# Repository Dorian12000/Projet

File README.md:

# Robot Chat et Souris

Ce projet consiste à créer un robot capable de jouer au jeu du chat et de la souris. Le robot est équipé de plusieurs fonctionnalités clés, notamment le contrôle de mouvement à l'aide de moteurs à courant continu (MCC), la localisation avec un Lidar YD X4, la détection du vide à l'aide de capteurs de bordure et le changement d'état ( Souris , Chat) grâce aux bumpers. 

## Schéma Fonctionnel : 
https://miro.com/app/dashboard/

## Fonctionnalités principales

1. **Contrôle de Mouvement (MCC) :**
   - Le robot est capable de se déplacer dans son environnement grâce à des moteurs à courant continu. 
2. **Localisation avec Lidar X4 :**
   - Utilisation du Lidar X4 pour permettre au robot de s'orienter et de se repérer dans son environnement.

3. **Détection du Vide avec Capteurs de Bordure et Changement d'état :**
   - Les capteurs de bordure sont utilisés pour détecter les zones sans sol, afin d'empêcher le robot de tomber.
   - Changement d'états (Souris, Chat) grâce aux bumpers : Utilisation de  bumpers placés sur chaque côté du robot. Lorsqu'un des bumpers est touché, on change  l'état du robot. 

## Utilisation

1. **Exécution du Programme :**
   - Pour démarrer le robot, exécutez le programme principal. Assurez-vous que toutes les dépendances sont installées et que le robot est correctement alimenté. Le robot démarre en mode Souris.

2. **Interface Utilisateur :**
   - Pour connaître les événements enregistrés par le robot, veuillez connecter une ST-link entre le robot et votre ordinateur, puis ouvrir une console (TeraTerm, Putty, ...) configurée en 115200 bauds.
   - Trois LEDs sont présentes sur le robot pour indiquer son état en temps réel :
        - Led verte :
        	- allumée : état chat
        	- éteinte : état souris
        - Led orange : changement d'état pour chaque détection de bordure.
        - Led rouge : le robot a rencontré un problème et doit être redémarré.

## Pilote Lidar pour système robotique

1. **Introduction :**

Le pilote Lidar consiste en l'intégration d'un lidar dans un système robotique tel que notre robot. Le lidar est utilisé pour la détection d'obstacles, la cartographie de l'environnement et la localisation des autres robots dans la zone d'opération. Ce document fournit des informations sur les fichiers principaux du projet, y compris les fichiers `drv_lidar.c`, `LidarTask.c`, et la création de la tâche Lidar.

2. **Contenu des fichiers :**

	#### `drv_lidar.c`

	Le fichier `drv_lidar.c` contient le code source pour le pilote du lidar. Il comprend les fonctionnalités suivantes :

	- **Initialisation du Lidar** : La fonction `LidarInit` initialise le lidar en configurant la communication UART, en créant un sémaphore pour la synchronisation des lectures UART, et en activant le l'échantillonage du lidar et son moteur.

	- **Communication UART** : Le fichier utilise la communication UART avec le mécanisme DMA pour une transmission et réception de données efficace et non bloquante.

	- **Commandes Lidar** : Les fonctions `LidarScanStart` et `LidarScanStop` envoient respectivement les commandes de démarrage et d'arrêt du scan au lidar.

	- **Traitement des données** : Les fonctions `getLidarScanData`, `checkCS` et `convertSample` sont responsables de la réception, de la vérification de la somme de contrôle et de la conversion des données de scan du lidar.

	- **Analyse des données Lidar** : La fonction `whereIsNearestRobot` analyse les données du lidar pour déterminer la position du robot le plus proche.

	- **Gestion des erreurs** : La fonction `LidarHealthStatus` permet d'obtenir le statut de santé du lidar et de gérer les erreurs éventuelles.

	- **Autres fonctionnalités** : Le fichier contient également des fonctions pour définir la vitesse du lidar, obtenir des informations sur le lidar et redémarrer le lidar.

	#### `LidarTask.c`

	Le fichier `LidarTask.c` contient la définition de la tâche Lidar. Il gère les états de la tâche, notamment l'initialisation du lidar, le scan, le traitement des données et le mode veille.

	- **États de la tâche** : Les états comprennent l'initialisation (`LIDAR_INIT`), le scan (`LIDAR_SCANNING`) et le mode veille (`LIDAR_STANDBY`).

	- **Initialisation** : La tâche commence par initialiser le lidar, récupérer des informations sur le lidar afin d'assurer son bon fonctionnement, puis passer à l'état de scan.

	- **Scan Lidar** : Dans cet état, la tâche démarre le scan du lidar, reçoit les données de scan, les traite et effectue des actions en fonction de l'état principal du système (CAT ou MOUSE).

	- **Mode veille** : Un état futur pour le mode veille est également prévu mais n'est pas encore implémenté.

	- **Gestion des erreurs** : En cas d'erreur lors du scan, la tâche passe à l'état d'erreur pour gérer la situation.

3. **Utilisation du code :**

	- **Création de la tâche Lidar** : La fonction `createLidarTask` dans `LidarTask.c` crée la tâche Lidar en utilisant FreeRTOS. Elle définit la profondeur de la pile et la priorité de la tâche.

	- **Configuration du Lidar** : Le fichier `drv_lidar.c` comprend des fonctions pour l'initialisation du lidar, la configuration de la vitesse du moteur, le démarrage et l'arrêt du scan, l'obtention d'informations, la récupération des données de scan, etc.

	- **Gestion des états** : La tâche Lidar gère différents états, tels que l'initialisation, le scan et la veille. Ces états sont définis dans `LidarTask.c` et peuvent être étendus selon les besoins.

	- **Analyse des données** : La fonction `whereIsNearestRobot` analyse les données du lidar pour déterminer la position du robot le plus proche. Cette fonction peut être adaptée en fonction des exigences spécifiques du projet.

4. **Remarques :**

	- Le pilote du lidar est conçu pour fonctionner avec FreeRTOS. Assurez-vous que votre projet est configuré pour utiliser FreeRTOS.

	- La communication avec le lidar utilise le DMA pour une transmission et une réception de données efficaces et non bloquantes via UART.

	- La fonction principale de la tâche Lidar est gérée par la fonction `lidarTask()`, qui comprend une machine d'états pour gérer les différents états du lidar.

	- La tâche Lidar s'exécute en boucle continue, surveillant et gérant l'état du dispositif lidar.

	- Des types de données personnalisés et des macros de journalisation sont définis dans `types.h` et `logger.h`, respectivement.

# Organisation des tâches 

Pour organiser nos tâches liées aux différentes fonctions du Lidar et des moteurs, nous avons crée une tache principale avec une priorité élevée ( code source dans mainTask.c). Cette tâche est divisé en plusieurs états :
   - Main Init : Initialisation des tâches de démarrage du Lidar, des moteurs et de l'asservissement.
   - ERROR : Gestion d'erreur
   - Mouse : Test de l'état avec une Led
   - CAT : Test de l'état avec une Led
( Pour l'état CAT/MOUSE, des notifications sont générées lorsque les bumpers sont appuyés)

Chaque état implique l'appels des tâches et des fonctions nécessaires. Un timer est configuré pour suivre l'état actuel du robot.

## Contrôle moteur et asservissement en vitesse

Les deux MCC sont controlés par des pwm et asservis en vitesse par un correcteur proportionnel dans une tâche.

1. **Driver de moteur :**

   Les fichiers `moteur_drv.c/.h` contiennent les fonctions permettant de commander la vitesse ainsi que les directions des moteurs et de générer les pwm en conséquence. Ils prévoient aussi le calcul de la vitesse des moteurs et la lecture des encodeurs.

2. **Conversion de la position visée en commande de vitesse pour les moteurs :**

   	Cette tâche reçoit une structure comprenant la position (angle et distance) à laquelle doit se rendre le robot. Ces données sont interprétées pour générer une commande (vitesse et sens de rotation) pour chaque moteur. La commande est ensuite utilisée pour l'asservissement en vitesse.

3. **Asservissement en vitesse :**

	La boucle d'asservissement en vitesse se fait toutes les 500 ms et comprend :

	- Récupération de la commande en vitesse en fonction de la position visée.
	- La lecture des encodeurs.
	- Le calcul de l'erreur entre la mesure et la commande en vitesse.
	- Le calcul de la nouvelle commande en vitesse par le correcteur proportionnel.
	- Transmission de la nouvelle commande de vitesse pour générer les pwm.

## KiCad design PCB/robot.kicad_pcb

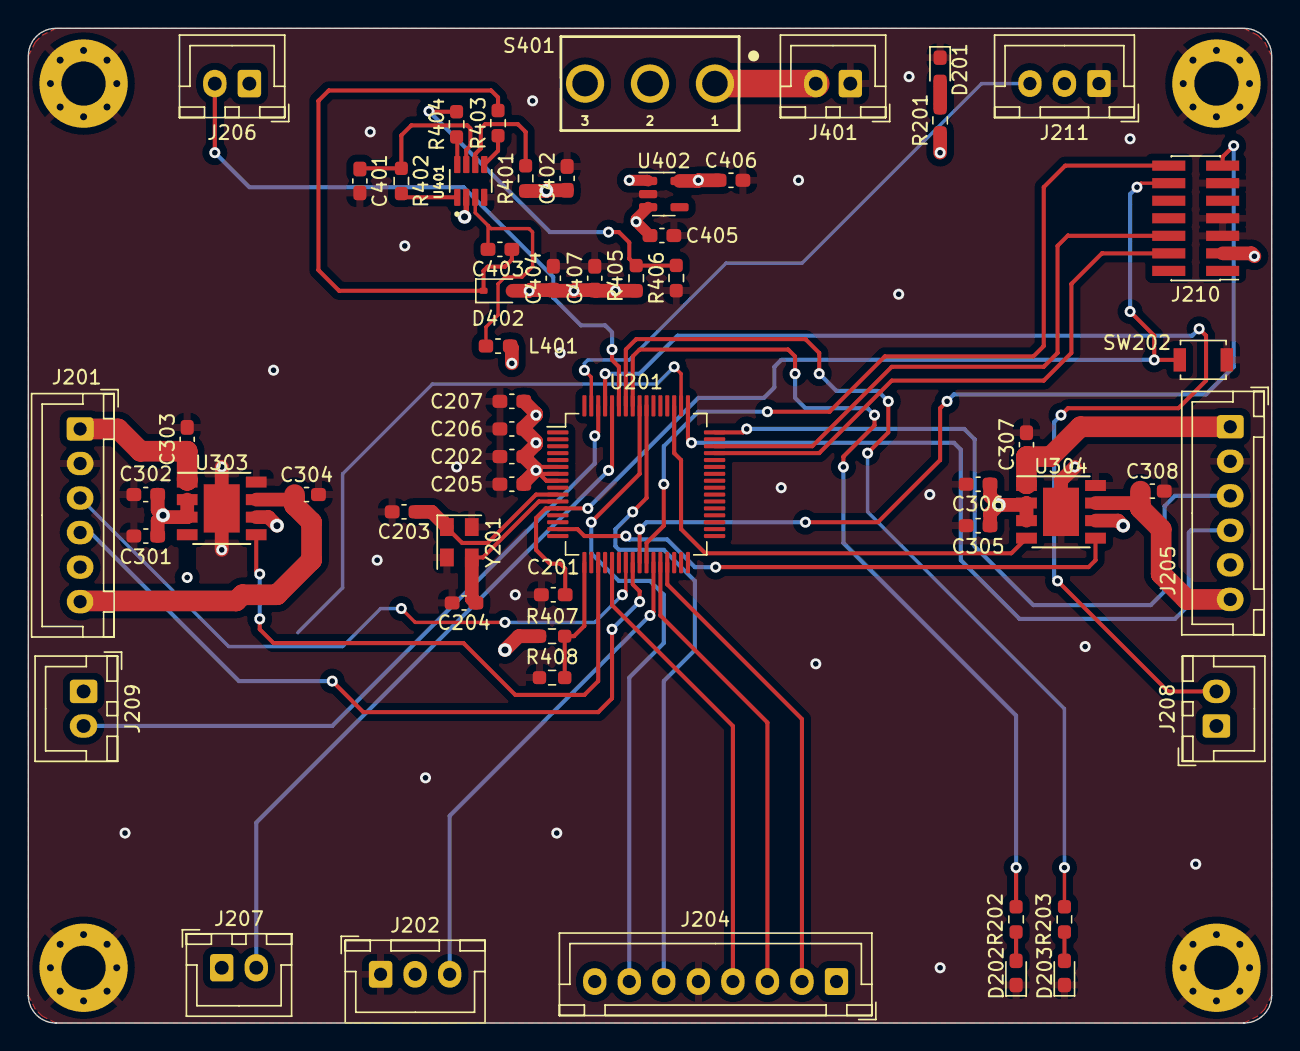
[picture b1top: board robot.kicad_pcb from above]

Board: 4 copper layers, 90.0 x 72.0 mm, 61 parts (0 on the bottom side), 49 nets.

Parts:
C201, C202, C205, C206: 100nF; C_0603_1608Metric_Pad1.08x0.95mm_HandSolder
C203, C204: 10pF; C_0603_1608Metric_Pad1.08x0.95mm_HandSolder
C207: 4.7uF; C_0603_1608Metric_Pad1.08x0.95mm_HandSolder
C301, C305, C405, C406: 1uF; C_0603_1608Metric_Pad1.08x0.95mm_HandSolder
C302, C306: 10uF; C_0603_1608Metric_Pad1.08x0.95mm_HandSolder
C303, C304, C307, C308: 10nF; C_0603_1608Metric_Pad1.08x0.95mm_HandSolder
C401: 0.1uF; C_0603_1608Metric_Pad1.08x0.95mm_HandSolder
C402, C404, C407: 22uF; C_0603_1608Metric_Pad1.08x0.95mm_HandSolder
C403: 100n; C_0603_1608Metric_Pad1.08x0.95mm_HandSolder
D201: LED G; LED_0603_1608Metric_Pad1.05x0.95mm_HandSolder
D202: LED R; LED_0603_1608Metric_Pad1.05x0.95mm_HandSolder
D203: LED B; LED_0603_1608Metric_Pad1.05x0.95mm_HandSolder
D402: 1N4148WS; D_SOD-323
H201, H202, H203, H204: MountingHole_Pad; MountingHole_3.2mm_M3_Pad_Via
J201: Motor_L; JST_XH_B6B-XH-A_1x06_P2.50mm_Vertical
J202: bordure_R; JST_XH_B3B-XH-A_1x03_P2.50mm_Vertical
J204: LIDAR; JST_XH_B8B-XH-A_1x08_P2.50mm_Vertical
J205: Motor_R; JST_XH_B6B-XH-A_1x06_P2.50mm_Vertical
J206: BUMPER_F; JST_XH_B2B-XH-A_1x02_P2.50mm_Vertical
J207: BUMPER_B; JST_XH_B2B-XH-A_1x02_P2.50mm_Vertical
J208: BUMPER_R; JST_XH_B2B-XH-A_1x02_P2.50mm_Vertical
J209: BUMPER_L; JST_XH_B2B-XH-A_1x02_P2.50mm_Vertical
J210: Conn_02x07_Odd_Even; PinHeader_2x07_P1.27mm_Vertical_SMD
J211: bordure_F; JST_XH_B3B-XH-A_1x03_P2.50mm_Vertical
J401: Conn_BAT; JST_XH_B2B-XH-A_1x02_P2.50mm_Vertical
L401: 4.7uH; L_0603_1608Metric_Pad1.05x0.95mm_HandSolder
R201, R202, R203: 1k; R_0603_1608Metric_Pad0.98x0.95mm_HandSolder
R401, R402: 100k; R_0603_1608Metric_Pad0.98x0.95mm_HandSolder
R403: 20; R_0603_1608Metric_Pad0.98x0.95mm_HandSolder
R404: 16k; R_0603_1608Metric_Pad0.98x0.95mm_HandSolder
R405: 40.2k; R_0603_1608Metric_Pad0.98x0.95mm_HandSolder
R406: 13k; R_0603_1608Metric_Pad0.98x0.95mm_HandSolder
R407: 12k; R_0603_1608Metric_Pad0.98x0.95mm_HandSolder
R408: 10k; R_0603_1608Metric_Pad0.98x0.95mm_HandSolder
S401: 472121010111
SW202: SW_Push; SW_SPST_B3U-1000P
U201: STM32G070RBTx; LQFP-64_10x10mm_P0.5mm
U303, U304: ZXBM5210-SP; Diodes_SO-8EP
U401: MP1475DJ-LF-P
U402: MIC5317; SOT-23-5
Y201: 16M; Crystal_SMD_EuroQuartz_MT-4Pin_3.2x2.5mm

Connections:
7.2V: C301.2, C302.1, C305.2, C306.1, C402.1, R401.1, R407.1, S401.2, U303.2 (VM), U303.3 (VDD), U303.6 (VREF), U304.2 (VM), U304.3 (VDD), U304.6 (VREF), U401.2 (IN)
+3.3V: C202.1, C205.2, C206.2, C207.2, C406.1, J201.5, J202.2, J205.5, J206.1, J207.1, J208.1, J209.1, J210.3, J211.2, R201.1, U201.6 (VBAT), U201.7 (VREF+), U201.8 (VDD), U402.5 (VOUT)
+5V: C404.1, C405.1, C407.1, D402.2 (A), J204.8, L401.2, R405.2, U402.1 (VIN), U402.3 (~SHDN)
/Motor/FWD_ML: U201.50 (PD0), U303.4 (FWD)
/Motor/FWD_MR: U201.51 (PD1), U304.4 (FWD)
/Motor/M_L1: C303.1, J201.1, U303.1 (OUT1)
/Motor/M_L2: C304.1, J201.6, U303.7 (OUT2)
/Motor/M_R1: C307.1, J205.1, U304.1 (OUT1)
/Motor/M_R2: C308.1, J205.6, U304.7 (OUT2)
/Motor/REV_ML: U201.19 (PA2), U303.5 (REV)
/Motor/REV_MR: U201.15 (PC2), U304.5 (REV)
/Power/BAT_LVL: R407.2, R408.1, U201.17 (PA0)
/STM32/BUMPER_B: J207.2, U201.60 (PB6)
/STM32/BUMPER_F: J206.2, U201.59 (PB5)
/STM32/BUMPER_L: J209.2, U201.62 (PB8)
/STM32/BUMPER_R: J208.2, U201.61 (PB7)
/STM32/DEV_EN: J204.3, U201.28 (PB1)
/STM32/Endoder_LA: J201.3, U201.23 (PA6)
/STM32/Endoder_LB: J201.4, U201.24 (PA7)
/STM32/Endoder_RA: J205.4, U201.49 (PC9)
/STM32/Endoder_RB: J205.3, U201.48 (PC8)
/STM32/LED_B: R203.1, U201.58 (PB4)
/STM32/LED_R: R202.1, U201.57 (PB3)
/STM32/LIDAR_RX: J204.6, U201.55 (PD5)
/STM32/LIDAR_TX: J204.7, U201.56 (PD6)
/STM32/M_EN: J204.2, U201.29 (PB2)
/STM32/M_SCTR: J204.4, U201.21 (PA4)
/STM32/NRST: C201.1, J210.12, SW202.2, U201.12 (NRST)
/STM32/OSC_IN: C203.1, U201.10 (PF0), Y201.1
/STM32/SWCLK: J210.6, U201.46 (PA14)
/STM32/SWDIO: J210.4, U201.45 (PA13)
/STM32/VCP_RX: J210.14, U201.26 (PC5)
/STM32/VCP_TX: J210.13, U201.25 (PC4)
/STM32/V_BORDURE_F: J211.3, U201.63 (PB9)
/STM32/V_BORDURE_R: J202.3, U201.27 (PB0)
GND: C201.2, C202.2, C203.2, C204.2, C205.1, C206.1, C207.1, C301.1, C302.2, C303.2, C304.2, C305.1, C306.2, C307.2, C308.2, C401.2, C402.2, C404.2, C405.2, C406.2, C407.2, D201.1 (K), D202.1 (K), D203.1 (K), H201.1, H202.1, H203.1, H204.1, J201.2, J202.1, J204.5, J205.2, J210.5, J210.7, J210.11, J211.1, J401.1, R406.1, R408.2, SW202.1, U201.9 (VSS), U303.8 (GND), U303.9 (GND), U304.8 (GND), U304.9 (GND), U401.4 (GND), U402.2 (GND), Y201.2, Y201.4
unnamed: D201.2 (A), R201.2
unnamed: D202.2 (A), R202.2
unnamed: D203.2 (A), R203.2
unnamed: C403.1, D402.1 (K), R403.2
unnamed: J401.2, S401.1
unnamed: R404.2, R405.1, R406.2
unnamed: C204.1, U201.11 (PF1), Y201.3
unnamed: R403.1, U401.5 (BST)
unnamed: R401.2, U401.6 (EN/SYNC)
unnamed: R404.1, U401.8 (FB)
unnamed: R402.2, U401.1 (PG)
unnamed: C403.2, L401.1, U401.3 (SW)
unnamed: C401.1, R402.1, U401.7 (VCC)

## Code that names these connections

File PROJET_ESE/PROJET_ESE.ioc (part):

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Mcu.Name=STM32G070RBTx
Mcu.Package=LQFP64
Mcu.UserName=STM32G070RBTx
PA0.GPIOParameters=GPIO_Label
PA0.GPIO_Label=ADC1_IN0 BAT_LVL
PA0.Mode=IN0
PA0.Signal=ADC1_IN0
PA13.Mode=Serial_Wire
PA13.Signal=SYS_SWDIO
PA14-BOOT0.Mode=Serial_Wire
PA14-BOOT0.Signal=SYS_SWCLK
PA2.GPIOParameters=GPIO_Label
PA2.GPIO_Label=TIM15_CH1 REV_ML
PA2.Signal=S_TIM15_CH1
PA4.GPIOParameters=GPIO_Label
PA4.GPIO_Label=TIM14_CH1 M_SCTR
PA4.Signal=S_TIM14_CH1
PA6.GPIOParameters=GPIO_Label
PA6.GPIO_Label=TIM3_CH1 ENCODER_LA
PA6.Signal=S_TIM3_CH1
PA7.GPIOParameters=GPIO_Label
PA7.GPIO_Label=TIM3_CH2 ENCODER_LB
PA7.Signal=S_TIM3_CH2
PB0.GPIOParameters=GPIO_PuPd,GPIO_Label
PB0.GPIO_Label=V_BORDURE_R
PB0.GPIO_PuPd=GPIO_PULLDOWN
PB0.Signal=GPIO_Input
PB1.GPIOParameters=GPIO_Label
PB1.GPIO_Label=DEV_EN
PB1.Signal=GPIO_Output
PB2.GPIOParameters=GPIO_Label
PB2.GPIO_Label=M_EN
PB2.Signal=GPIO_Output
PB3.GPIOParameters=PinState,GPIO_Label
PB3.GPIO_Label=LED_R
PB3.PinState=GPIO_PIN_SET
PB3.Signal=GPIO_Output
PB4.GPIOParameters=PinState,GPIO_Label
PB4.GPIO_Label=LED_B
PB4.PinState=GPIO_PIN_SET
PB4.Signal=GPIO_Output
PB5.GPIOParameters=GPIO_PuPd,GPIO_Label
PB5.GPIO_Label=BUMPER_F
PB5.GPIO_PuPd=GPIO_PULLDOWN
PB5.Signal=GPIO_Input
PB6.GPIOParameters=GPIO_PuPd,GPIO_Label
PB6.GPIO_Label=BUMPER_B
PB6.GPIO_PuPd=GPIO_PULLDOWN
PB6.Signal=GPIO_Input
PB7.GPIOParameters=GPIO_PuPd,GPIO_Label
PB7.GPIO_Label=BUMPER_R
PB7.GPIO_PuPd=GPIO_PULLDOWN
PB7.Signal=GPIO_Input
PB8.GPIOParameters=GPIO_PuPd,GPIO_Label
PB8.GPIO_Label=BUMPER_L
PB8.GPIO_PuPd=GPIO_PULLDOWN
PB8.Signal=GPIO_Input
PB9.GPIOParameters=GPIO_PuPd,GPIO_Label
PB9.GPIO_Label=V_BORDURE_F
PB9.GPIO_PuPd=GPIO_PULLDOWN
PB9.Signal=GPIO_Input
PC2.GPIOParameters=GPIO_Label
PC2.GPIO_Label=TIM15_CH2 REV_MR
PC2.Signal=S_TIM15_CH2
PC4.GPIOParameters=GPIO_Label
PC4.GPIO_Label=USART1_TX VCP_TX
PC4.Mode=Asynchronous
PC4.Signal=USART1_TX
PC5.GPIOParameters=GPIO_Label
PC5.GPIO_Label=USART1_RX VCP_RX
PC5.Mode=Asynchronous
PC5.Signal=USART1_RX
PC8.GPIOParameters=GPIO_Label
PC8.GPIO_Label=TIM1_CH1 ENCODER_RB
PC8.Signal=S_TIM1_CH1
PC9.GPIOParameters=GPIO_Label
PC9.GPIO_Label=TIM1_CH2 ENCODER_RA
PC9.Signal=S_TIM1_CH2
PD0.GPIOParameters=GPIO_Label
PD0.GPIO_Label=TIM16_CH1 FWD_ML
PD0.Signal=S_TIM16_CH1
PD1.GPIOParameters=GPIO_Label
PD1.GPIO_Label=TIM17_CH1 FWD_MR
PD1.Signal=S_TIM17_CH1
PD5.GPIOParameters=GPIO_Label
PD5.GPIO_Label=USART2_TX LIDAR_TX
PD5.Mode=Asynchronous
PD5.Signal=USART2_TX
PD6.GPIOParameters=GPIO_Label
PD6.GPIO_Label=USART2_RX LIDAR_RX
PD6.Mode=Asynchronous
PD6.Signal=USART2_RX
PF0-OSC_IN\ (PF0).Mode=HSE-External-Oscillator
PF0-OSC_IN\ (PF0).Signal=RCC_OSC_IN
PF1-OSC_OUT\ (PF1).Mode=HSE-External-Oscillator
PF1-OSC_OUT\ (PF1).Signal=RCC_OSC_OUT
RCC.HSE_VALUE=8000000
RCC.SYSCLKFreq_VALUE=64000000
RCC.SYSCLKSource=RCC_SYSCLKSOURCE_PLLCLK
board=custom

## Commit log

2023-09-18 add: bom
2023-09-18 chore: bom
2023-09-18 chore: remove line
2023-09-18 chore: capteur de bordure
2023-09-18 add: docs
2023-09-18 chore: reg 5V
2023-09-18 chore: add led on bom
2023-09-18 add: kicad project
2023-09-18 schéma fonctionnel
2023-09-18 add: icon
2023-09-19 add: shematic
2023-09-19 chore: pcb
2023-09-19 chore: ignore PCB folder
2023-09-19 chore: pcb batterie lvl
2023-09-19 schema
2023-09-20 chore: readme header
2023-09-20 chore: update readme
2023-09-20 update kicad
2023-09-20 CUBE
2023-09-20 add: image
2023-09-21 chore: update pcb
2023-09-21 chore: mounting via pcb
2023-09-21 add: log
2023-09-21 add: lidar dev manual
2023-09-25 chore: schematic review
2023-09-25 test
2023-09-25 ajout branche
2023-09-25 update: schematic
2023-09-28 chore: routage
2023-09-28 update: routage
2023-09-28 lidar motor function
2023-09-28 Doc Lidar
2023-09-28 Lidar define
2023-09-28 lidar struct
2023-10-02 fix: lidar.c
2023-10-02 update: drv lidar
2023-10-02 update: PCB
2023-10-05 add : test motor
2023-10-05 chore: lidar devID
2023-10-05 add : pmw files
2023-10-05 pwm files
2023-10-05 Lidar ScanTest
2023-10-05 health Status
2023-10-09 gitignore update
2023-10-09 delete
2023-10-09 Macros
2023-10-09 chore: uart optimisation
2023-10-09 chore: uart
2023-10-09 chore: lidar command
2023-10-16 chore: optimisation
2023-10-16 add: state machine
2023-10-16 update: state machine
2023-10-16 chore: semaphore
2023-10-16 chore: gitignore
2023-10-25 chore: .h improvement
2023-11-13 improvement: lidar
2023-11-23 chore: update
2023-11-24 chore: samples convertion
2023-12-01 chore: lidar improvement
2023-12-01 start battery level
2023-12-04 chore: freeRTOS
2023-12-04 add: main Task
2023-12-04 add: bumper ISR
2023-12-08 Update AuxiliaryTask partie batterie
2023-12-18 chore: interrupt
2023-12-18 add: gitignore
2023-12-18 chore: delete files
2023-12-18 chore: to delete
2023-12-18 chore: delete file
2023-12-18 add: lidar file
2023-12-18 fix: path
2023-12-19 chore: doxygen
2023-12-19 Algo Chat_Souris
2023-12-19 Battery function canceled due to fault on ground plan
2023-12-19 AlgoChatSouris
2023-12-20 nouveau pin
2023-12-20 Meilleure organisation parce que Dorianne a fait de la merde
2023-12-21 Project Test PCB du Prof
2024-01-08 Project Test PCB du Prof et Test Recup data lidar
2024-01-08 fix: lidar config
2024-01-11 Gael-Laksan Test
2024-01-11 Test des Bumpers,Bordure,Moteur avec FreeRTOS
2024-01-14 chore: readme general
2024-01-14 chore: quelques modif de code
2024-01-14 chore: lidar documentation
2024-01-14 fix: numerotation
2024-01-14 fix: tabulation
2024-01-17 documentation doxygen
